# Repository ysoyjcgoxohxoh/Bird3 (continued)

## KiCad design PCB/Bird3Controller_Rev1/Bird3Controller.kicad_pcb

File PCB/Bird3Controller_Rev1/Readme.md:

> [!NOTE]
> This board does drive the scooter, but it has some issues. This revision is not recommended.

## Errata ##
- Physical
  - The mounting holes are in slightly incorrect locations.
- LCD
  - LCD connector is wired in reverse.
  - The LCD mounting cutouts are not quite big enough, causing a very tight fit when clipping on the LCD.
  - The LCD mounting is missing alignment holes.
  - The data lines to the LCD span two registers, necessitating jumper wires for compatibility with the `TFT_eSPI` library.
- Power
  - There are two 3.3v nets, causing half the board to be unpowered.
  - 3.3v is insufficient for the headlight driver.
- Headlight
  - The headlight driver's current is set too low.
  - The headlight driver's inductor physically interferes with LCD.

## Board Renderings ##

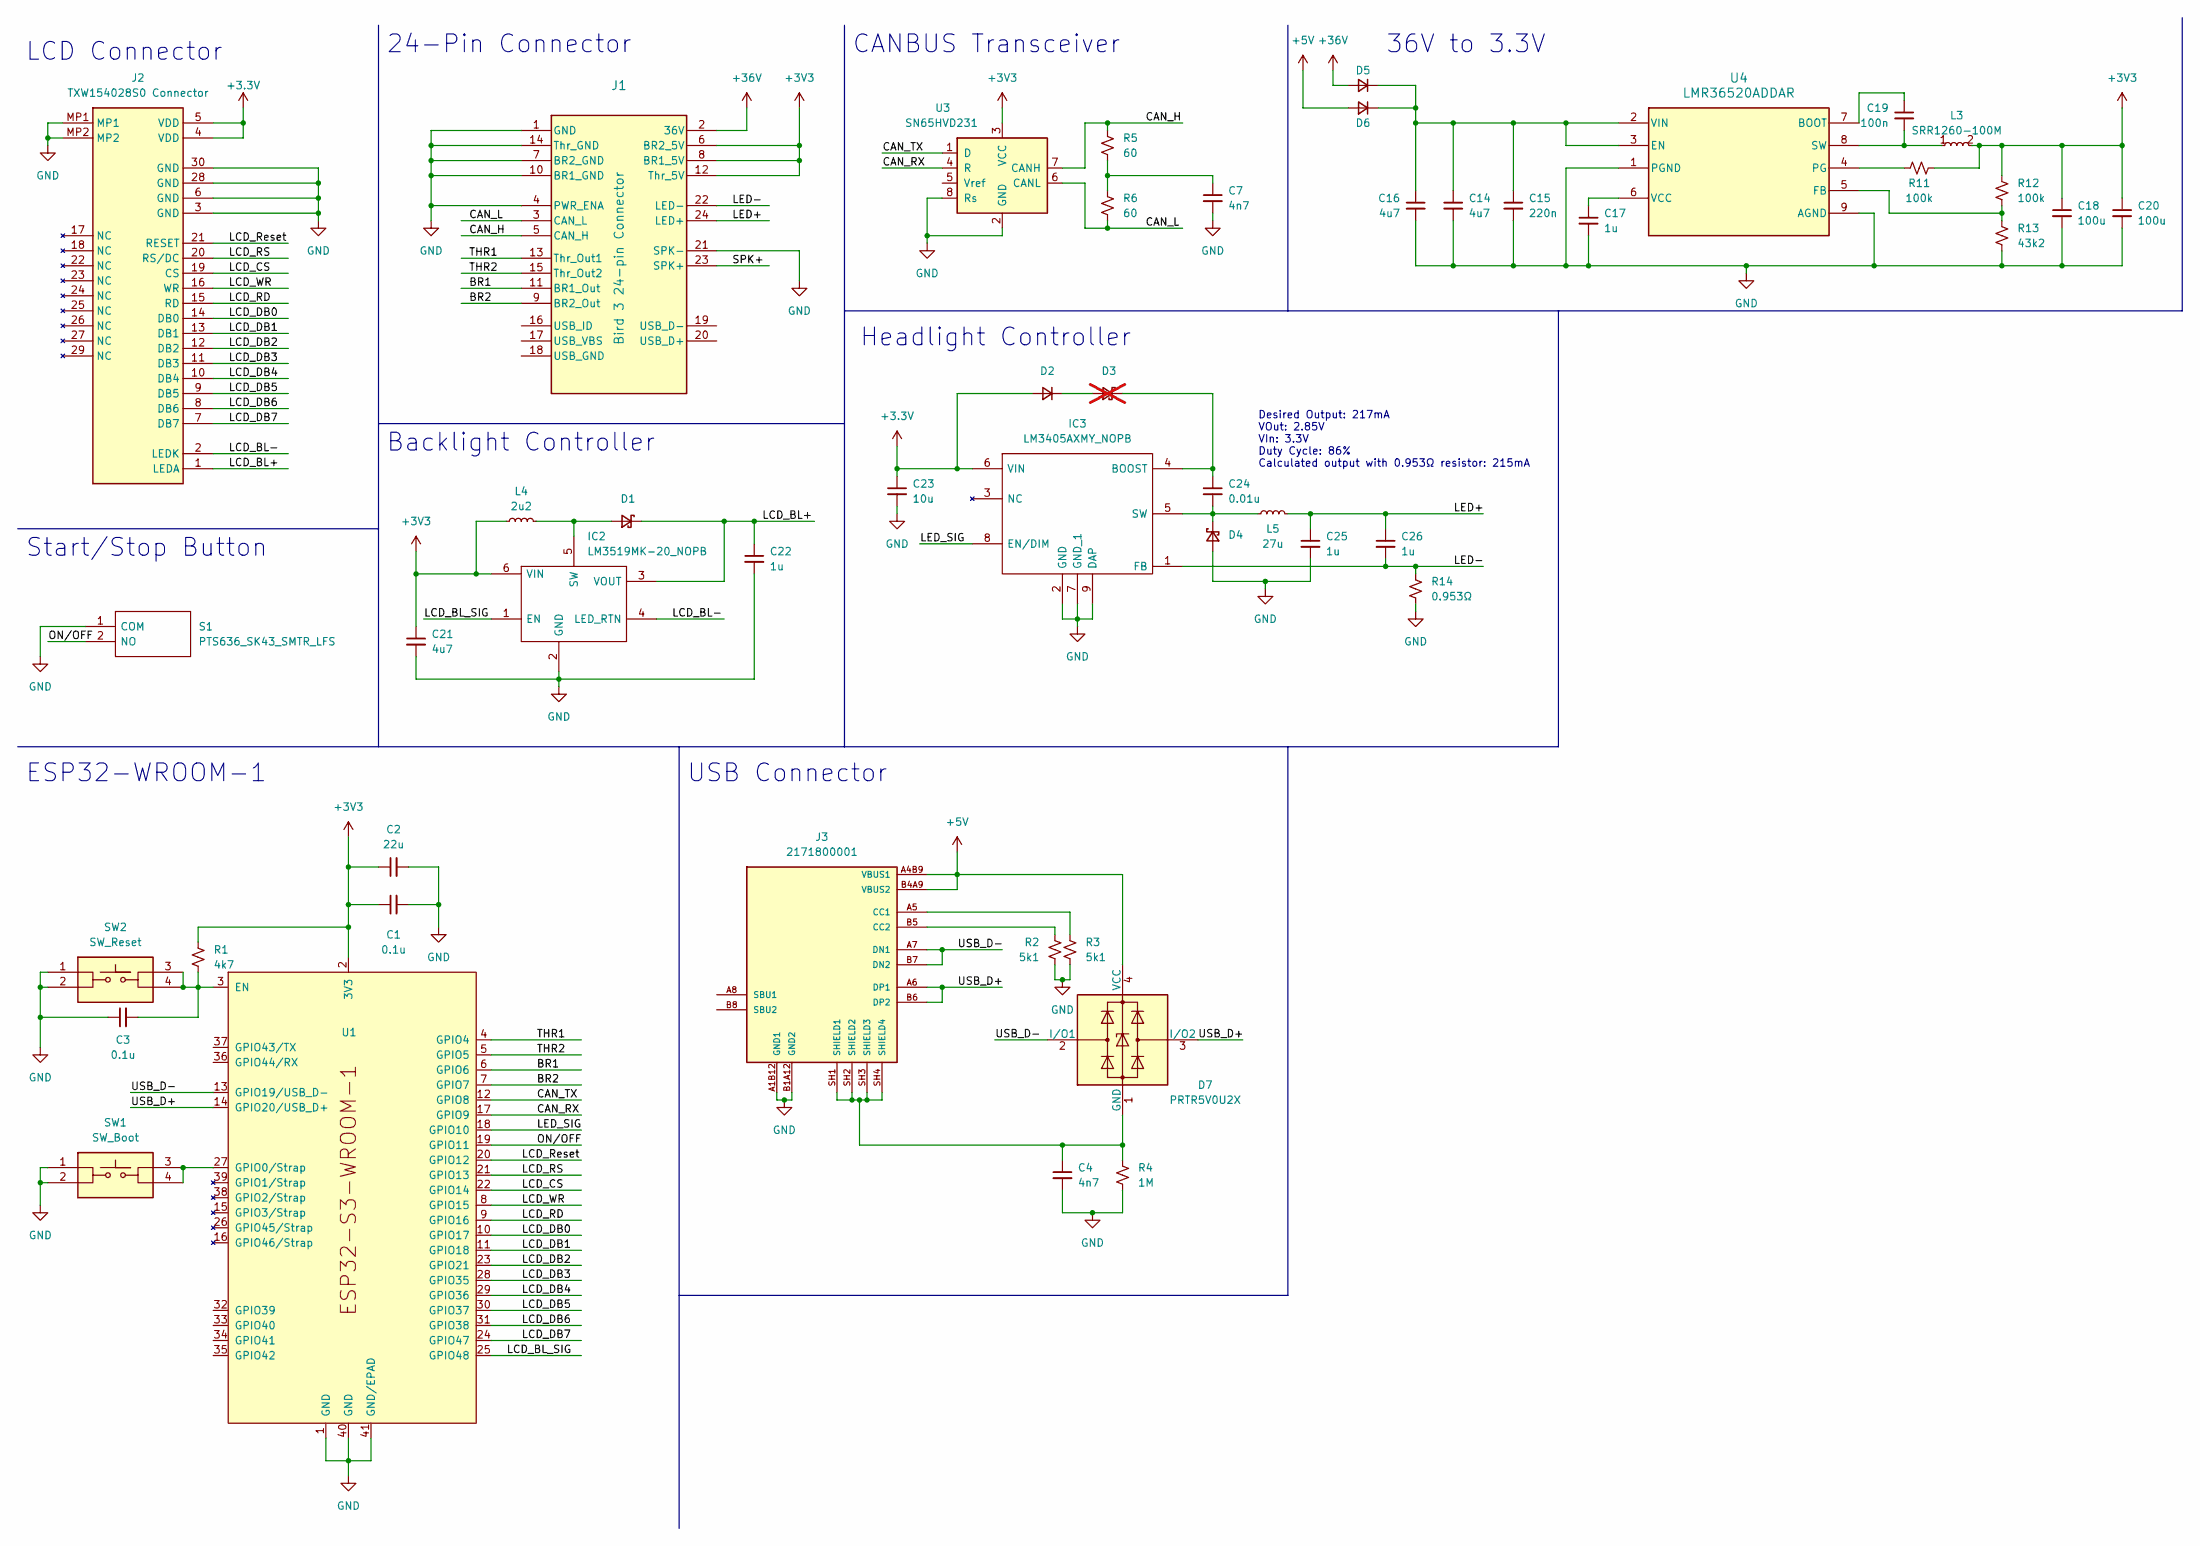
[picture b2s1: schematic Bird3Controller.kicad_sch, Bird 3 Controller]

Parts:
C1, C3: 0.1u; C_0805_2012Metric_Pad1.18x1.45mm_HandSolder; Mouser Part Number 603-AC0805JX7R9BB104
C2: 22u; C_0805_2012Metric_Pad1.18x1.45mm_HandSolder; Mouser Part Number 81-GRT21BR61C226ME3L
C4, C7: 4n7; C_0805_2012Metric_Pad1.18x1.45mm_HandSolder; Mouser Part Number 581-08055C472K4T4A
C14, C16, C21: 4u7; C_1210_3225Metric_Pad1.33x2.70mm_HandSolder; Mouser Part Number 187-CL32Y475MCIVPNE
C15: 220n; C_0805_2012Metric_Pad1.18x1.45mm_HandSolder; Mouser Part Number 581-08053C224K4T4A
C17, C22, C25, C26: 1u; C_0805_2012Metric_Pad1.18x1.45mm_HandSolder; Mouser Part Number 187-CL21B105MBFNNNE
C18, C20: 100u; C_0805_2012Metric_Pad1.18x1.45mm_HandSolder; Mouser Part Number 187-CL21A107MQYNNWE
C19: 100n; C_0805_2012Metric_Pad1.18x1.45mm_HandSolder; Mouser Part Number 603-AC0805JX7R9BB104
C23: 10u; C_0805_2012Metric_Pad1.18x1.45mm_HandSolder; Mouser Part Number 81-GRT21BC71E106KE13
C24: 0.01u; C_0805_2012Metric_Pad1.18x1.45mm_HandSolder; Mouser Part Number 581-KAM21BR72A103KT
D1, D4: D_Schottky_Small; D_0805_2012Metric_Pad1.15x1.40mm_HandSolder; Mouser Part Number 581-SD0805S020S1R0
D2: D_Small; D_0805_2012Metric_Pad1.15x1.40mm_HandSolder; Mouser Part Number 833-1N4148WX-TP
D3: D_Schottky_Small; D_0805_2012Metric_Pad1.15x1.40mm_HandSolder; not fitted
D5, D6: GS1J_R1_00001; DIOM5027X244M; Mouser Part Number 241-GS1J_R1_00001
D7: PRTR5V0U2X; SOT-143; Mouser Part Number 771-PRTR5V0U2X-QR
IC2: LM3519MK-20_NOPB; SOT95P280X110-6N; Mouser Part Number 926-LM3519MK-20/NOPB
IC3: LM3405AXMY_NOPB; SOP65P490X109-9N; Mouser Part Number 926-LM3405AXMY/NOPB
J1: Bird 3 24-pin Connector; CONN_87832-2420_MOL; Mouser Part Number 538-87832-6123
J2: TXW154028S0 Connector; FH34SRJ30S05SH50; Mouser Part Number 798-FH34SRJ30S05SH50
J3: 2171800001; MOLEX_2171800001; PARTREV A1; Mouser Part Number 538-217180-0001
L3: SRR1260-100M; SRR1260100M; Mouser Part Number 652-SRR1260-100M
L4: 2u2; INDC2520X100N; Mouser Part Number 652-CVH252009-2R2M
L5: 27u; SRR1240270M; Mouser Part Number 652-SRR1240-270M
R1: 4k7; R_0805_2012Metric_Pad1.20x1.40mm_HandSolder; Mouser Part Number 71-CRCW0805J-4.7K-E3
R2, R3: 5k1; R_0805_2012Metric_Pad1.20x1.40mm_HandSolder; Mouser Part Number 71-CRCW08055K10FKEAC
R4: 1M; R_0805_2012Metric_Pad1.20x1.40mm_HandSolder; Mouser Part Number 71-RCS08051M00JNEA
R5, R6: 60; R_0805_2012Metric_Pad1.20x1.40mm_HandSolder; Mouser Part Number 71-RCS080560R4FKEA
R11, R12: 100k; R_0805_2012Metric_Pad1.20x1.40mm_HandSolder; Mouser Part Number 71-RCS0805100KFKEA
R13: 43k2; R_0805_2012Metric_Pad1.20x1.40mm_HandSolder; Mouser Part Number 71-CRCW080543K2FKEAC
R14: 0.953Ω; R_0805_2012Metric_Pad1.20x1.40mm_HandSolder; Mouser Part Number 279-RLC73K2AR953FTDF
S1: PTS636_SK43_SMTR_LFS; PTS636SK43SMTRLFS; Mouser Part Number 611-PTS636SK43SMTRLF
SW1: SW_Boot; PTS526SK15SMTR2LFS; Mouser Part Number 611-PTS526SK15SMR2L
SW2: SW_Reset; PTS526SK15SMTR2LFS; Mouser Part Number 611-PTS526SK15SMR2L
U1: ESP32-S3-WROOM-1; Mouser Part Number 356-EP32S3WROOM1N8R8
U3: SN65HVD231; SOIC-8_3.9x4.9mm_P1.27mm; Mouser Part Number 595-SN65HVD231DRG4
U4: LMR36520ADDAR; SOIC127P600X170-9N; Mouser Part Number 595-LMR36520ADDAR

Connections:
+3V3: C1.1, C2.1, C18.1, C20.1, C21.1, IC2.6 (VIN), J1.6 (BR2_5V), J1.8 (BR1_5V), J1.12 (Thr_5V), L3.2, L4.1, R1.2, R11.2, R12.2, U1.2 (3V3), U3.3 (VCC)
+5V: D6.2 (A), D7.4 (VCC), J3.A4B9 (VBUS1), J3.B4A9 (VBUS2)
+36V: D5.2 (A), J1.2 (36V)
/BR1: J1.11 (BR1_Out), U1.6 (GPIO6)
/BR2: J1.9 (BR2_Out), U1.7 (GPIO7)
/CAN_H: J1.5 (CAN_H), R5.1, U3.7 (CANH)
/CAN_L: J1.3 (CAN_L), R6.2, U3.6 (CANL)
/CAN_RX: U1.17 (GPIO9), U3.4 (R)
/CAN_TX: U1.12 (GPIO8), U3.1 (D)
/LCD_BL+: C22.1, D1.1 (K), IC2.3 (VOUT), J2.1 (LEDA)
/LCD_BL-: IC2.4 (LED_RTN), J2.2 (LEDK)
/LCD_BL_SIG: IC2.1 (EN), U1.25 (GPIO48)
/LCD_CS: J2.19 (CS), U1.22 (GPIO14)
/LCD_DB0: J2.14 (DB0), U1.10 (GPIO17)
/LCD_DB1: J2.13 (DB1), U1.11 (GPIO18)
/LCD_DB2: J2.12 (DB2), U1.23 (GPIO21)
/LCD_DB3: J2.11 (DB3), U1.28 (GPIO35)
/LCD_DB4: J2.10 (DB4), U1.29 (GPIO36)
/LCD_DB5: J2.9 (DB5), U1.30 (GPIO37)
/LCD_DB6: J2.8 (DB6), U1.31 (GPIO38)
/LCD_DB7: J2.7 (DB7), U1.24 (GPIO47)
/LCD_RD: J2.15 (RD), U1.9 (GPIO16)
/LCD_RS: J2.20 (RS/DC), U1.21 (GPIO13)
/LCD_Reset: J2.21 (RESET), U1.20 (GPIO12)
/LCD_WR: J2.16 (WR), U1.8 (GPIO15)
/LED+: C25.1, C26.1, J1.24 (LED+), L5.2
/LED-: C26.2, IC3.1 (FB), J1.22 (LED-), R14.1
/LED_SIG: IC3.8 (EN/DIM), U1.18 (GPIO10)
/ON/OFF: S1.2 (NO), U1.19 (GPIO11)
/SPK+: J1.23 (SPK+)
/THR1: J1.13 (Thr_Out1), U1.4 (GPIO4)
/THR2: J1.15 (Thr_Out2), U1.5 (GPIO5)
/USB_D+: D7.3 (I/O2), J3.A6 (DP1), J3.B6 (DP2), U1.14 (GPIO20/USB_D+)
/USB_D-: D7.2 (I/O1), J3.A7 (DN1), J3.B7 (DN2), U1.13 (GPIO19/USB_D-)
GND: C1.2, C2.2, C3.1, C4.2, C7.2, C14.2, C15.2, C16.2, C17.2, C18.2, C20.2, C21.2, C22.2, C23.2, C25.2, D4.2 (A), IC2.2 (GND), IC3.2 (GND), IC3.7 (GND_1), IC3.9 (DAP), J1.1 (GND), J1.4 (PWR_ENA), J1.7 (BR2_GND), J1.10 (BR1_GND), J1.14 (Thr_GND), J1.21 (SPK-), J2.3 (GND), J2.6 (GND), J2.28 (GND), J2.30 (GND), J2.MP1, J2.MP2, J3.A1B12 (GND1), J3.B1A12 (GND2), R2.2, R3.2, R4.2, R13.1, R14.2, S1.1 (COM), SW1.1, SW1.2, SW2.1, SW2.2, U1.1 (GND), U1.40 (GND), U1.41 (GND/EPAD), U3.2 (GND), U3.8 (Rs), U4.1 (PGND), U4.9 (AGND)
unnamed: C7.1, R5.2, R6.1
unnamed: D1.2 (A), IC2.5 (SW), L4.2
unnamed: C24.1, D3.1 (K), IC3.4 (BOOST)
unnamed: C24.2, D4.1 (K), IC3.5 (SW), L5.1
unnamed: C14.1, C15.1, C16.1, D5.1 (K), D6.1 (K), U4.2 (VIN), U4.3 (EN)
unnamed: C4.1, D7.1 (GND), J3.SH1 (SHIELD1), J3.SH2 (SHIELD2), J3.SH3 (SHIELD3), J3.SH4 (SHIELD4), R4.1
unnamed: J3.A5 (CC1), R3.1
unnamed: J3.B5 (CC2), R2.1
unnamed: C3.2, R1.1, SW2.3, SW2.4, U1.3 (EN)
unnamed: SW1.3, SW1.4, U1.27 (GPIO0/Strap)
unnamed: C19.1, U4.7 (BOOT)
unnamed: R12.1, R13.2, U4.5 (FB)
unnamed: R11.1, U4.4 (PG)
unnamed: C19.2, L3.1, U4.8 (SW)
unnamed: C17.1, U4.6 (VCC)

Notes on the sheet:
Headlight Controller
36V to 3.3V
ESP32-WROOM-1
CANBUS Transceiver
Desired Output: 217mA VOut: 2.85V VIn: 3.3V Duty Cycle: 86% Calculated output with 0.953Ω resistor: 215mA
24-Pin Connector
LCD Connector
Backlight Controller
USB Connector
Start/Stop Button

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
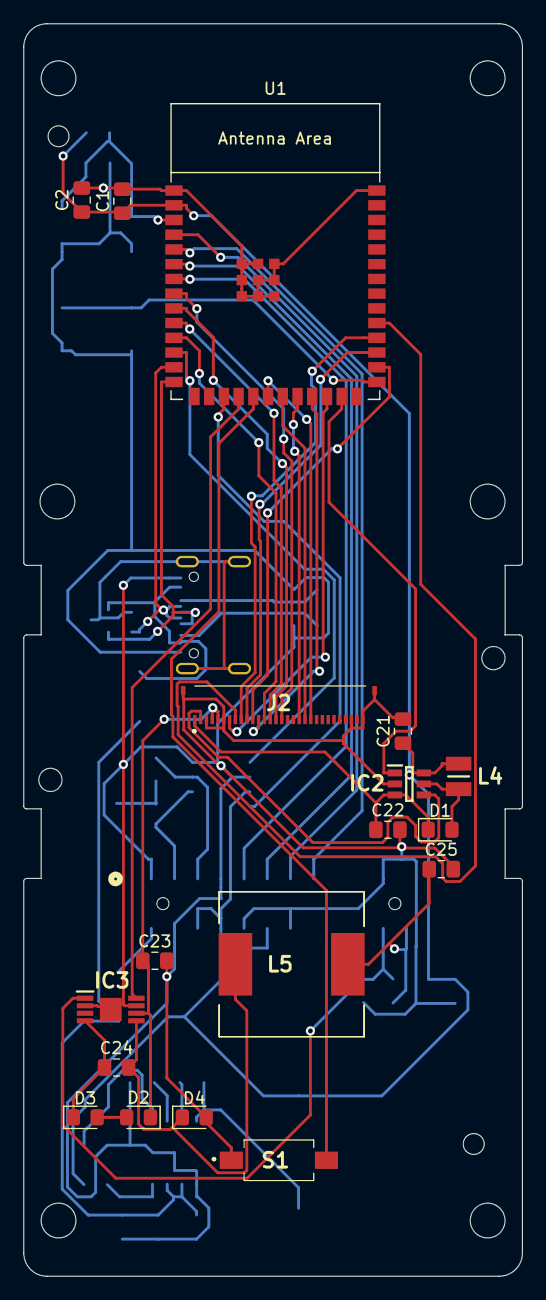
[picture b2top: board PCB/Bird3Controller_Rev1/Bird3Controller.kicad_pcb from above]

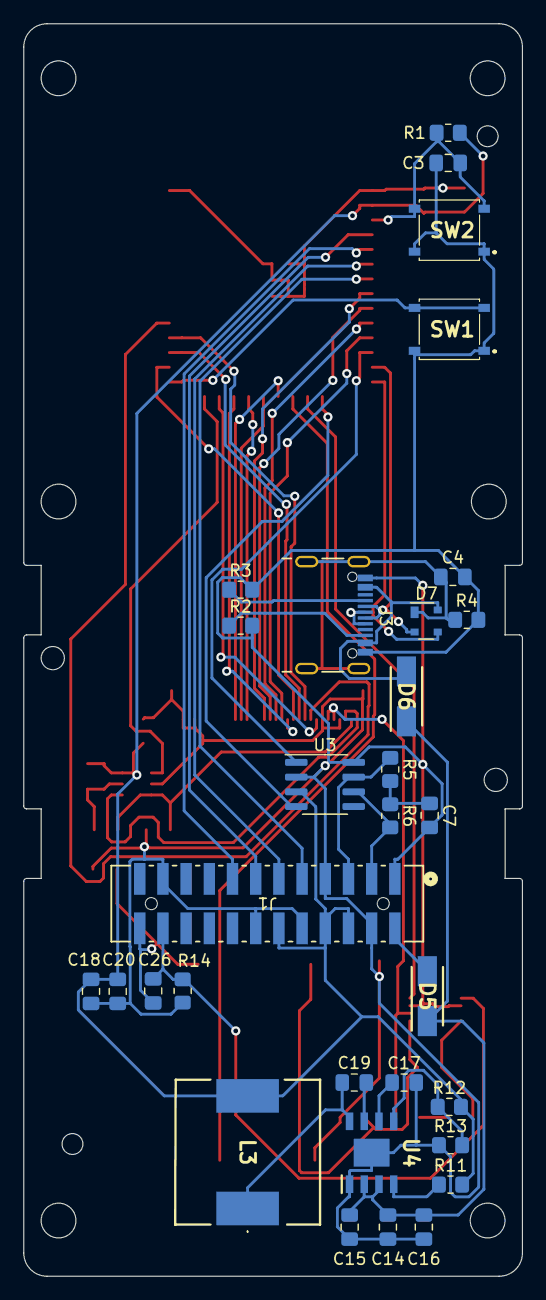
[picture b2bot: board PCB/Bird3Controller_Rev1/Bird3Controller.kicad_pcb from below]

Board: 2 copper layers, 43.0 x 108.0 mm, 49 parts (31 on the bottom side), 51 nets.

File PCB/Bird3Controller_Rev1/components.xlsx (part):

Refs | Datasheet | Description | Footprint | Value | Manufacturer_Name | Manufacturer_Part_Number | Mouser Part Number | Mouser Price/Stock | Digikey Part Number | JLCPCB Part
C18 | https://www.mouser.com/datasheet/2/585/Samsung_7_14_2022_CL2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 |  | Capacitor_SMD:C_0805_2012Metric_Pad1.18x1.45mm_HandSolder | 100u | Samsung Electro-Mechanics | CL21A107MQYNNWE | 187-CL21A107MQYNNWE |  | 1276-CL21A107MQYNNWECT-ND | C141660
C20 | https://www.mouser.com/datasheet/2/585/Samsung_7_14_2022_CL2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 |  | Capacitor_SMD:C_0805_2012Metric_Pad1.18x1.45mm_HandSolder | 100u | Samsung Electro-Mechanics | CL21A107MQYNNWE | 187-CL21A107MQYNNWE |  | 1276-CL21A107MQYNNWECT-ND | C141660
C17 | https://www.mouser.com/datasheet/2/585/MLCC-1837944.pdf |  | Capacitor_SMD:C_0805_2012Metric_Pad1.18x1.45mm_HandSolder | 1u | Samsung Electro-Mechanics | CL21B105MBFNNNE | 187-CL21B105MBFNNNE |  | 1276-1029-1-ND | C28323
C22 | https://www.mouser.com/datasheet/2/585/MLCC-1837944.pdf |  | Capacitor_SMD:C_0805_2012Metric_Pad1.18x1.45mm_HandSolder | 1u | Samsung Electro-Mechanics | CL21B105MBFNNNE | 187-CL21B105MBFNNNE |  | 1276-1029-1-ND | C28323
C25 | https://www.mouser.com/datasheet/2/585/MLCC-1837944.pdf |  | Capacitor_SMD:C_0805_2012Metric_Pad1.18x1.45mm_HandSolder | 1u | Samsung Electro-Mechanics | CL21B105MBFNNNE | 187-CL21B105MBFNNNE |  | 1276-1029-1-ND | C28323
C26 | https://www.mouser.com/datasheet/2/585/MLCC-1837944.pdf |  | Capacitor_SMD:C_0805_2012Metric_Pad1.18x1.45mm_HandSolder | 1u | Samsung Electro-Mechanics | CL21B105MBFNNNE | 187-CL21B105MBFNNNE |  | 1276-1029-1-ND | C28323
C14 | https://www.mouser.com/datasheet/2/585/MLCC_Automotive-1837966.pdf |  | Capacitor_SMD:C_1210_3225Metric_Pad1.33x2.70mm_HandSolder | 4u7 | Samsung Electro-Mechanics | CL32Y475MCIVPNE | 187-CL32Y475MCIVPNE |  | 1276-CL32Y475KCIVPNECT-ND | C385986
C16 | https://www.mouser.com/datasheet/2/585/MLCC_Automotive-1837966.pdf |  | Capacitor_SMD:C_1210_3225Metric_Pad1.33x2.70mm_HandSolder | 4u7 | Samsung Electro-Mechanics | CL32Y475MCIVPNE | 187-CL32Y475MCIVPNE |  | 1276-CL32Y475KCIVPNECT-ND | C385986
C21 | https://www.mouser.com/datasheet/2/585/MLCC_Automotive-1837966.pdf |  | Capacitor_SMD:C_1210_3225Metric_Pad1.33x2.70mm_HandSolder | 4u7 | Samsung Electro-Mechanics | CL32Y475MCIVPNE | 187-CL32Y475MCIVPNE |  | 1276-CL32Y475KCIVPNECT-ND | C385986
D5 | https://www.mouser.co.uk/datasheet/2/1057/GS1A_SERIES-1870033.pdf |  | Bird3Controller:DIOM5027X244M | GS1J_R1_00001 | PANJIT | GS1J_R1_00001 | 241-GS1J_R1_00001 | https://www.mouser.co.uk/ProductDetail/Panjit/GS1J_R1_00001?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 | 3757-GS1J_R1_00001CT-ND | C241929
D6 | https://www.mouser.co.uk/datasheet/2/1057/GS1A_SERIES-1870033.pdf |  | Bird3Controller:DIOM5027X244M | GS1J_R1_00001 | PANJIT | GS1J_R1_00001 | 241-GS1J_R1_00001 | https://www.mouser.co.uk/ProductDetail/Panjit/GS1J_R1_00001?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 | 3757-GS1J_R1_00001CT-ND | C241929
R14 | https://www.mouser.com/datasheet/2/418/9/ENG_DS_1773269_3_C-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 |  | Resistor_SMD:R_0805_2012Metric_Pad1.20x1.40mm_HandSolder | 0.953Î© | TE Connectivity / CGS | RLC73K2AR953FTDF | 279-RLC73K2AR953FTDF |  | 1712-RLC73K2AR953FTDCT-ND | C400704
U1 | https://www.espressif.com/sites/default/files/documentation/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 |  | Bird3Controller:ESP32-S3-WROOM-1 | ESP32-S3-WROOM-1 | Espressif Systems | ESP32-S3-WROOM-1-N8R8 | 356-EP32S3WROOM1N8R8 |  | 1965-ESP32-S3-WROOM-1-N8R8CT-ND | C2913201
J3 |  |  | Bird3Controller:MOLEX_2171800001 | 2171800001 | Molex | 217180-0001 | 538-217180-0001 |  | 900-2171800001CT-ND
J1 | 878322420 |  | Bird3Controller:CONN_87832-2420_MOL | Bird 3 24-pin Connector | Molex | 87832-6123 | 538-87832-6123 |  | WM18646-ND
C15 | https://www.mouser.com/datasheet/2/40/AutoMLCC-2952695.pdf |  | Capacitor_SMD:C_0805_2012Metric_Pad1.18x1.45mm_HandSolder | 220n | KYOCERA AVX | 08053C224K4T4A | 581-08053C224K4T4A |  | 478-KAM21KR71E224KUCT-ND | C5153
C4 | https://www.mouser.com/datasheet/2/40/AutoMLCC-2952695.pdf |  | Capacitor_SMD:C_0805_2012Metric_Pad1.18x1.45mm_HandSolder | 4n7 | KYOCERA AVX | 08055C472K4T4A | 581-08055C472K4T4A |  | 478-KAM21KR71E224KUCT-ND | C117979
C7 | https://www.mouser.com/datasheet/2/40/AutoMLCC-2952695.pdf |  | Capacitor_SMD:C_0805_2012Metric_Pad1.18x1.45mm_HandSolder | 4n7 | KYOCERA AVX | 08055C472K4T4A | 581-08055C472K4T4A |  | 478-KAM21KR71E224KUCT-ND | C117979
C24 | https://www.mouser.com/datasheet/2/40/AutoMLCCKAM-3216307.pdf |  | Capacitor_SMD:C_0805_2012Metric_Pad1.18x1.45mm_HandSolder | 0.01u | KYOCERA AVX | KAM21BR72A103KT | 581-KAM21BR72A103KT |  | 478-KAM21BR72A103KTCT-ND | C469523
D1 | https://www.mouser.com/datasheet/2/40/schottky-3165252.pdf |  | Diode_SMD:D_0805_2012Metric_Pad1.15x1.40mm_HandSolder | D_Schottky_Small | KYOCERA AVX | SD0805S020S1R0 | 581-SD0805S020S1R0 |  | 478-7800-1-ND | C143773
D4 | https://www.mouser.com/datasheet/2/40/schottky-3165252.pdf |  | Diode_SMD:D_0805_2012Metric_Pad1.15x1.40mm_HandSolder | D_Schottky_Small | KYOCERA AVX | SD0805S020S1R0 | 581-SD0805S020S1R0 |  | 478-7800-1-ND | C143773
U4 | https://www.ti.com/lit/gpn/lmr36520 |  | Bird3Controller:SOIC127P600X170-9N | LMR36520ADDAR | Texas Instruments | LMR36520ADDAR | 595-LMR36520ADDAR |  | 296-LMR36520ADDARCT-ND | C1858393
U3 | http://www.ti.com/lit/ds/symlink/sn65hvd230.pdf |  | Package_SO:SOIC-8_3.9x4.9mm_P1.27mm | SN65HVD231 | Texas Instruments | SN65HVD231DRG4 | 595-SN65HVD231DRG4 |  | 296-15380-1-ND | C129257
C1 | https://www.mouser.com/datasheet/2/447/UPY_AC_NP0X7RX7S_6_3V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 |  | Capacitor_SMD:C_0805_2012Metric_Pad1.18x1.45mm_HandSolder | 0.1u | YAGEO | AC0805JRX7R9BB104 | 603-AC0805JX7R9BB104 |  | 13-AC0805JRX7R9BB104CT-ND
C19 | https://www.mouser.com/datasheet/2/447/UPY_AC_NP0X7RX7S_6_3V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 |  | Capacitor_SMD:C_0805_2012Metric_Pad1.18x1.45mm_HandSolder | 100n | YAGEO | AC0805JRX7R9BB104 | 603-AC0805JX7R9BB104 |  | 13-AC0805JRX7R9BB104CT-ND
C3 | https://www.mouser.com/datasheet/2/40/AutoMLCC-2952695.pdf |  | Capacitor_SMD:C_0805_2012Metric_Pad1.18x1.45mm_HandSolder | 0.1u | YAGEO | AC0805JRX7R9BB104 | 603-AC0805JX7R9BB104 |  | 13-AC0805JRX7R9BB104CT-ND
SW1 | https://www.ckswitches.com/media/2780/pts526.pdf |  | Bird3Controller:PTS526SK15SMTR2LFS | SW_Boot | C & K COMPONENTS | PTS526 SK15 SMTR2 LFS | 611-PTS526SK15SMR2L | https://www.mouser.co.uk/ProductDetail/CK/PTS526-SK15-SMTR2-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 | CKN12221-1-ND | C2689521
SW2 | https://www.ckswitches.com/media/2780/pts526.pdf |  | Bird3Controller:PTS526SK15SMTR2LFS | SW_Reset | C & K COMPONENTS | PTS526 SK15 SMTR2 LFS | 611-PTS526SK15SMR2L | https://www.mouser.co.uk/ProductDetail/CK/PTS526-SK15-SMTR2-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 | CKN12221-1-ND | C2689521
S1 | https://componentsearchengine.com/Datasheets/1/PTS636 SK43 SMTR LFS.pdf | Tactile Switches Tact 50mA 12VDC, 6.0x3.5, 4.3mm H, 250gf, G leads, No ground p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 | Bird3Controller:PTS636SK43SMTRLFS | PTS636_SK43_SMTR_LFS | C & K COMPONENTS | PTS636 SK43 SMTR LFS | 611-PTS636SK43SMTRLF | https://www.mouser.co.uk/ProductDetail/CK/PTS636-SK43-SMTR-L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 | CKN12311-1-ND
L4 | https://www.mouser.com/datasheet/2/54/CVH-42677.pdf |  | Bird3Controller:INDC2520X100N | 2u2 | Bourns | CVH252009-2R2M | 652-CVH252009-2R2M |  | CVH252009-2R2MCT-ND | C840597
L5 | https://www.mouser.com/datasheet/2/54/SRR1240-1391459.pdf |  | Bird3Controller:SRR1240270M | 27u | Bourns | SRR1240-270M | 652-SRR1240-270M |  | SRR1240-270MCT-ND | C2047515
L3 | https://www.arrow.com/en/products/srr1260-100m/bourns?region=europe |  | Bird3Controller:SRR1260100M | SRR1260-100M | Bourns | SRR1260-100M | 652-SRR1260-100M | https://www.mouser.co.uk/ProductDetail/Bourns/SRR1260-100M?q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 | SRR1260-100MCT-ND | C3221699
R13 | https://www.vishay.com/docs/20035/dcrcwe3.pdf |  | Resistor_SMD:R_0805_2012Metric_Pad1.20x1.40mm_HandSolder | 43k2 | Vishay / Dale | CRCW0805150KFKEAC | 71-CRCW0805150KFKEAC |  | 541-CRCW0805150KFKEACCT-ND | C2077224
R2 | https://www.vishay.com/docs/20035/dcrcwe3.pdf |  | Resistor_SMD:R_0805_2012Metric_Pad1.20x1.40mm_HandSolder | 5k1 | Vishay / Dale | CRCW08055K10FKEAC | 71-CRCW08055K10FKEAC |  | 541-CRCW08055K10FKEACCT-ND | C844854
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
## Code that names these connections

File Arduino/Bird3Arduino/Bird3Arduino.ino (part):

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#ifdef Arduino_Nano_ESP32

// Communication Pins
#define CAN_RX_PIN 44  // RX0
#define CAN_TX_PIN 43  // TX1

// Inputs
#define THROTTLEA_PIN A0   // TR_WP1 - Increases as throttle is pressed, Connector Pin 13
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#ifdef ESP32BirdBrainRev1

// Communication Pins
#define CAN_RX_PIN     9   // ESP Pin 17
#define CAN_TX_PIN     8   // ESP Pin 12

// Inputs
#define THROTTLEA_PIN  4   // ESP Pin 4  - TR_WP1 - Increases as throttle is pressed, Connector Pin 13
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
// Outputs
#define HEADLIGHT_PIN  10  // ESP Pin 18 - Output to LED Driver. PWM in future, but for now, just on/off
#define LCD_BL_SIG     48  // ESP Pin 25 - Output to LCD Backlight driver

// LCD Pins
// Changes must be made in ..\libraries\TFT_eSPI\User_Setup.h starting at line 254
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#ifdef ESP32BirdBrainRev2

// Communication Pins
#define CAN_RX_PIN     9   // ESP Pin 17
#define CAN_TX_PIN     8   // ESP Pin 12
#define I2C_SDA        43  // ESP Pin 37 - I2C Serial Data Line
#define I2C_SCL        44  // ESP Pin 36 - I2C Serial Clock Line

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
// Outputs
#define HEADLIGHT_PIN  10  // ESP Pin 18 - Output to LED Driver. PWM in future, but for now, just on/off
#define LCD_BL_SIG     17  // ESP Pin 10 - Output to LCD Backlight driver
#define PWR_ENA_SIG    18  // ESP Pin 11 - Output to PWR_ENA mosfet. Pulling this high connects the PWR_ENA pin on the Bird connector to ground, waking up the ESC and possibly the BMS.

// LCD Pins
// Changes must be made in ..\libraries\TFT_eSPI\User_Setup.h starting at line 254
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    if (!driver_installed) {

      // Initialize configuration structures using macro initializers
      twai_general_config_t g_config = TWAI_GENERAL_CONFIG_DEFAULT((gpio_num_t)CAN_TX_PIN, (gpio_num_t)CAN_RX_PIN, TWAI_MODE_NO_ACK);
      twai_timing_config_t t_config = TWAI_TIMING_CONFIG_500KBITS();  //Look in the api-reference for other speed sets.
      twai_filter_config_t f_config = TWAI_FILTER_CONFIG_ACCEPT_ALL();

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  // Configure the headlight pin
  pinMode(HEADLIGHT_PIN, OUTPUT);
#ifdef PWR_ENA_SIG
  pinMode(PWR_ENA_SIG, OUTPUT);
  digitalWrite(PWR_ENA_SIG, HIGH);
#endif

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  icons.loadFont(icons28, sizeof(icons28));
  RedrawScreen();

  ledcAttachPin(LCD_BL_SIG, 4);
  ledcSetup(4, 30000, 8);
  ledcWrite(4, 30);

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
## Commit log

2023-10-07 Add .net Windows Forms application to unlock battery and control motor.
2023-10-07 Add readme
2023-10-08 Add basic sketch to use hardware timers and read the throttle.
2023-10-14 It works! A bunch has changed: It actually operates the scooter, there's a button to turn it off and on, an output for the headlight LED, and another set of keepalive messages for the EA00022 control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
2023-10-20 Add content to readme
2023-12-19 Delay the canbus initialization until the first button press to allow connecting the debug serial
2024-01-22 Tentative success with generating keepalive/uptime messages rather than storing them. This still uses a preconfigured last-four-bytes of the keepalive message, but we're getting somewhere now.
2024-01-22 Remove code dumps of keepalive codes now that we know what's actually important in them. Uptime is now a 32-bit integer
2024-01-22 Reset back to 0 when it would reach timerCounterMax rather than after it reaches it.
    Because: timerCounterMax = 5000. Tthe old logic resulted in events being processed when timerCounter equaled 5000 *and* when it equaled 0. This caused those events to be run double every five seconds.
2024-01-22 Receive the 0x60C message and use it to keep the BMS awake
2024-03-07 Clarify library source
2024-03-07 Reorganize pin definitions
2024-03-07 Use NO_ACK mode
2024-03-07 Read the messages for battery voltage and wheel/motor speed.
2024-03-07 Send keepalive once every five seconds
2024-03-07 Send braking message when right brake is pulled. It doesn't work yet, but it's here.
2024-03-07 Update Readme with more messages
2024-03-08 Add kicad PCB
2024-03-08 Update top speed in readme
2024-03-21 Add prototype schematic
2024-03-21 Support the custom Bird Brain board Revision 1
2024-03-21 Final Rev1 schematic update
2024-03-21 Add screen layout
2024-03-21 Add .dbc files
2024-03-21 Add modified verison of Bodmer's screenServer.ino for taking screenshots.
2024-03-21 Add datasheets
2024-03-21 Ignore a bunch of stuff
2024-03-21 Remove unnecessary cache
2024-03-21 Add components excel
2024-03-21 Ignore more stuff
2024-03-21 Add powershell testing functions
2024-03-21 Copy Rev1 for Rev2
2024-03-21 Add original schematic used on protoboard
2024-03-21 Add License
2024-03-21 Format definitions
2024-03-21 Rearrange and comment code
2024-03-21 Move Revision 1 to a more clearly named directory
2024-03-21 Add board renders
2024-03-21 Add Rev 1 Readme
2024-03-21 Update Readme with links to PCBs
2024-03-21 Rearrange .gitignore
2024-03-21 Update Rev1 readme
2024-03-22 Show renderings on Rev1 Readme
2024-03-22 Add Rev2 Readme
2024-03-22 Reduce keepalive interval to 1 second to attempt keeping the BMS from sleeping
2024-03-22 Ignore more files
2024-03-23 Update/organize Rev1 errata
2024-03-28 Add 22-pin connector, new headlight circuit, etc. for Rev 2
2024-03-28 Update Rev2 Readme
2024-03-30 Add circuit to selectively ground the `PWR_ENA` pin
2024-03-30 Add `PWR_ENA` mosfet and fuse to PCB
2024-03-30 Update PCB to use add PTC fuse on VIN
2024-03-30 Label USB connector pins
2024-03-30 Rearrange some things to remove some vias
2024-03-30 Upgrade Rev2 project and files to KiCad 8 using KiCad 8.0.1
2024-03-30 Adjust edge.cuts on the PCB and in the LCD connector footprint to remove overlapping lines that were creating trouble.
2024-03-30 Update PCB from schematic for first time since v8
2024-03-30 Add EEPROM to schematic and board.
    Also add the symbol, footprint, and 3D model
2024-03-30 Fix silkscreen for USB breakout header
2024-03-30 Move things around to eliminate two vias in the CAN_TX trace
2024-03-30 Push more things around
2024-03-30 Move vias around a bit
2024-03-30 Don't use thermal relief for SMD components
2024-03-30 Add more ground-plane vias
2024-03-30 Push LCD data traces around and add more ground plane vias
2024-03-30 Add silkscreen reference to github repo and a placement for the JLCPCB order number
2024-03-30 Update gerbers and rendering for Revision 2
2024-03-30 Update Readmes
2024-03-30 Add Mouser links and prices for all components
2024-03-30 Add Bill of Materials
2024-03-30 Add credits
2024-03-31 Add Development and Ordering information
2024-04-06 Fix part number that referred to 0.402ohm resistor instead of the correct 0.200ohm value
2024-04-06 Update schematic revision number
2024-04-06 Add interactive BOM using `InteractiveHtmlBOM` v2.9.0
2024-04-06 Write more reasonable debug message
2024-04-06 Add Rev2 schematic in both PDF and PNG forms
2024-04-06 Add bill of materials link
2024-04-06 Clarify comment
2024-04-06 Add background to symbols for consistency
2024-04-06 If `PWR_ENA_SIG` is defined, write an output to that pin to activate the mosfet to pull the `PWR_ENA` pin to ground.
2024-04-06 Update pin definition for Revision 2
2024-04-06 Update fields on PCB
2024-04-06 Use PWM for headlight
2024-04-06 Correct LCD rotation for Rev 2
2024-04-07 Update Rev2 Errata
2024-04-14 Add Revision 3
2024-04-14 Rearrange schematic
2024-04-14 Set copper edge clearance.
2024-04-14 Optimize ground plane/vias
2024-04-15 Shrink LCD Connector pads to reduce bridging
2024-04-15 Switch to thermal reliefs for pad connections except for thermal pads. Also move some traces around to optimize the thermal reliefs
2024-04-15 Rearrange and add ground plane vias
2024-04-15 Correct ESP32 thermal pad violations and the USB-C breakout text that keeps moving randomly
2024-04-15 Update footprints to better indicate pin 1
2024-04-15 Add test points
2024-04-16 Add Rev3 Gerbers
2024-04-16 Add missing test point names on silkscreen.
2024-04-17 Add `Rating` field, use lower cost VIN cap, add description to most components
2024-04-17 Add Revision 3 BOM
2024-04-25 Add basic RemoteXY BLE security. Add custom font with lock icon. Add enumeration for state and delay disabling BMS.
2024-05-05 Fix R12 and R13 label position
2024-05-05 Rename fields to work with `kicost`. Also, correct the Mouser Part Number for C15.
2024-05-05 Add interactive BOM
2024-05-05 Add Rev3 Schematic image and pdf and update Rev3 Readme
